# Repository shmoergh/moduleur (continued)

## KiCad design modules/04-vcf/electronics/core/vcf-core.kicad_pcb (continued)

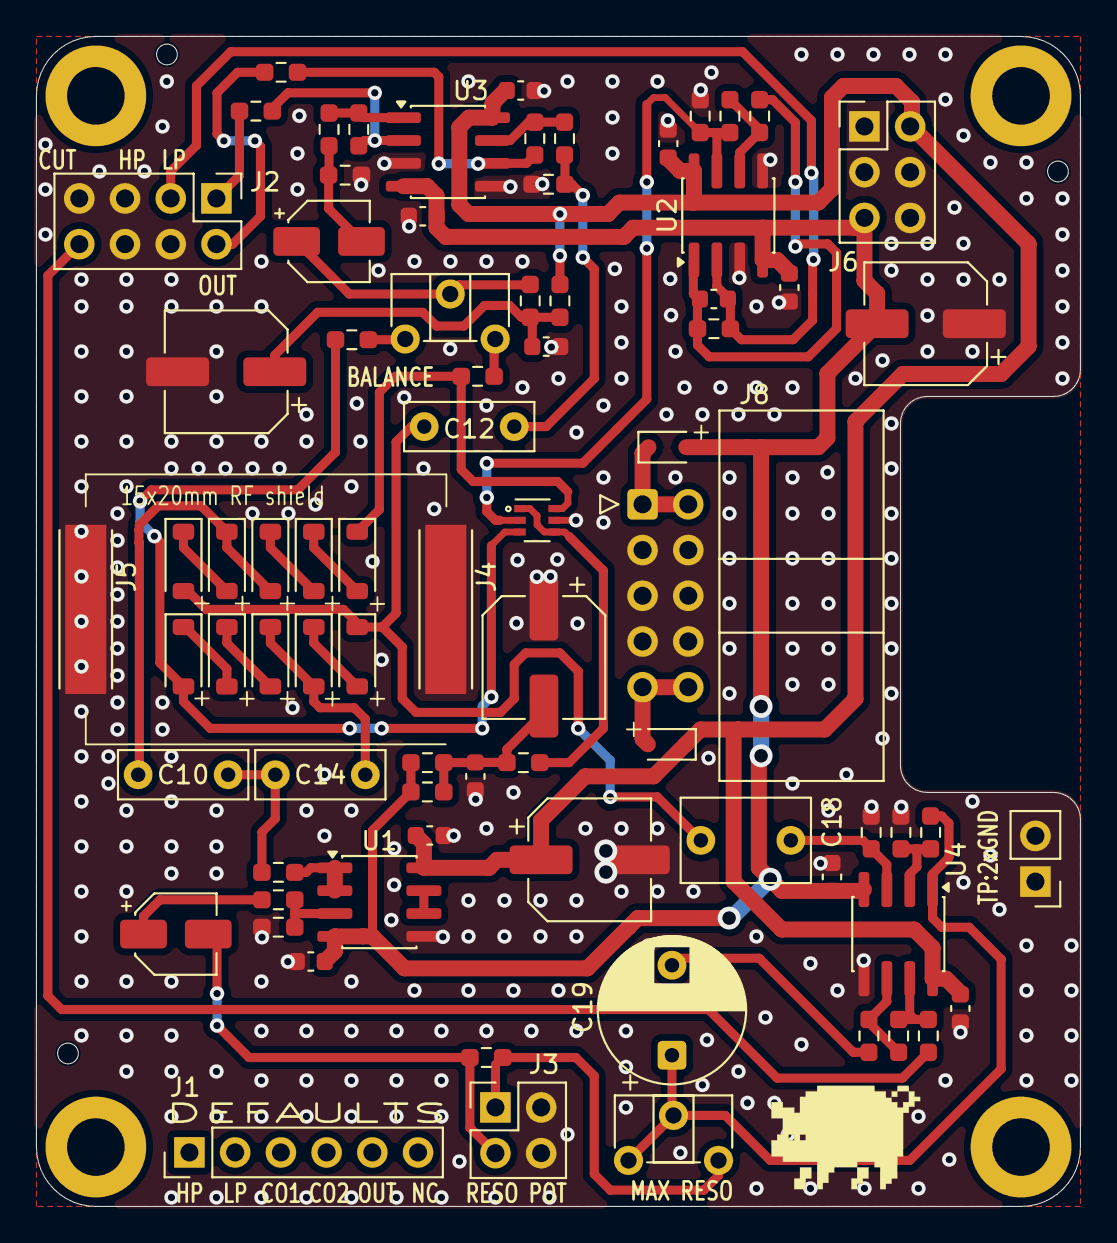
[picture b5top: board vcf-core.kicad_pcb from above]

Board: 2 copper layers, 58.0 x 65.0 mm, 82 parts (0 on the bottom side), 48 nets.

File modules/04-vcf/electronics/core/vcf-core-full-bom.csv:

"Reference","Qty","Value","Exclude from BOM","Footprint","LCSC","Part no.","Part URL","Vendor","CHECKED"
"C1,C2,C3,C4,C5,C6,C8,C9,C15,C16","10","100n","","Capacitor_SMD:C_0603_1608Metric","C14663","","","JLCPCB","YES"
"C7","1","10n","","Capacitor_SMD:C_0603_1608Metric","C57112","","","JLCPCB","YES"
"C10,C12,C14","3","1n (Foil)","","Capacitor_THT:C_Rect_L7.0mm_W2.5mm_P5.00mm","","80-R82EC1100SH50J ","https://mou.sr/3ZRLX4F","Mouser","YES"
"C11","1","2.2u","","Capacitor_SMD:CP_Elec_4x5.7","C249889","","","JLCPCB","YES"
"C13,C17,C21,C22","4","100u","","Capacitor_SMD:CP_Elec_6.3x7.7","C2836442","","","JLCPCB","YES"
"C18","1","1u (foil)","","Capacitor_THT:C_Rect_L7.0mm_W4.5mm_P5.00mm","","80-R82CC4100AA60J ","https://mou.sr/48MjAbl","Mouser","YES"
"C19","1","4.7u","","Capacitor_THT:CP_Radial_D8.0mm_P5.00mm","","80-ESK475M035AC3AA ","https://mou.sr/455uZSu","Mouser","YES"
"C20","1","10u","","Capacitor_SMD:CP_Elec_4x5.4","C3343","","","JLCPCB","YES"
"D1,D2,D3,D4,D5,D6,D7,D8,D9,D10","10","1N4148","","Diode_SMD:D_SOD-123","C81598","","","JLCPCB","YES"
"D11,D12","2","1N5817","","Diode_SMD:D_SOD-323","C5190152","","","JLCPCB","YES"
"H1,H2,H3,H4","4","MountingHole","Excluded from BOM","MountingHole:MountingHole_3.2mm_M3_DIN965_Pad","","","","X",""
"J1","1","Conn_01x06","","Connector_PinHeader_2.54mm:PinHeader_1x06_P2.54mm_Vertical","","200-SSW10401TMS","https://mou.sr/4puxA0F","Mouser","YES"
"J2","1","Conn_02x04_Counter_Clockwise","","Connector_PinHeader_2.54mm:PinHeader_2x04_P2.54mm_Vertical","","200-HTSW10407TD ","https://mou.sr/4nYsZDt","Mouser","YES"
"J3","1","Conn_02x02_Counter_Clockwise","","Connector_PinHeader_2.54mm:PinHeader_2x02_P2.54mm_Vertical","","200-HTSW10207TD","https://mou.sr/3TDBcz9","Mouser","YES"
"J4,J5","2","S1711-46R","Excluded from BOM","Shmoergh_Custom_Footprints:HARWIN_S1711-46R","","855-S1711-46R ","https://mou.sr/44w0zrg","Mouser","YES"
"J6","1","Conn_02x03_Odd_Even","","Connector_PinHeader_2.54mm:PinHeader_2x03_P2.54mm_Vertical","","200-TSW10307TD","https://mou.sr/4liCQlU","Mouser","YES"
"J7","1","Conn_01x02","","Connector_PinHeader_2.54mm:PinHeader_1x02_P2.54mm_Vertical","","200-HTSW10207TS","https://mou.sr/3IruU3e","Mouser","YES"
"J8","1","Conn_02x05_Odd_Even","","Connector_IDC:IDC-Header_2x05_P2.54mm_Horizontal","","571-5103310-1","https://mou.sr/3GwYxj9","Mouser","YES"
"Q1","1","BC847BS","","Package_TO_SOT_SMD:SOT-363_SC-70-6","C5380687","","","JLCPCB","YES"
"R1","1","20k","","Resistor_SMD:R_0603_1608Metric_Pad0.98x0.95mm_HandSolder","C4184","","","JLCPCB","YES"
"R4,R6,R8,R29","4","10k","","Resistor_SMD:R_0603_1608Metric_Pad0.98x0.95mm_HandSolder","C25804","","","JLCPCB","YES"
"R7","1","56k","","Resistor_SMD:R_0603_1608Metric_Pad0.98x0.95mm_HandSolder","C23206","","","JLCPCB","YES"
"R9,R26","2","47k","","Resistor_SMD:R_0603_1608Metric_Pad0.98x0.95mm_HandSolder","C25819","","","JLCPCB","YES"
"R10","1","200k","","Resistor_SMD:R_0603_1608Metric_Pad0.98x0.95mm_HandSolder","C25811","","","JLCPCB","YES"
"R11","1","180k","","Resistor_SMD:R_0603_1608Metric_Pad0.98x0.95mm_HandSolder","C3016400","","","JLCPCB","YES"
"R12","1","2.7k","","Resistor_SMD:R_0603_1608Metric_Pad0.98x0.95mm_HandSolder","C13167","","","JLCPCB","YES"
"R13,R22","2","1.5k","","Resistor_SMD:R_0603_1608Metric_Pad0.98x0.95mm_HandSolder","C22843","","","JLCPCB","YES"
"R14","1","2.2k","","Resistor_SMD:R_0603_1608Metric_Pad0.98x0.95mm_HandSolder","C4190","","","JLCPCB","YES"
"R15","1","33k","","Resistor_SMD:R_0603_1608Metric_Pad0.98x0.95mm_HandSolder","C4216","","","JLCPCB","YES"
"R16","1","100","","Resistor_SMD:R_0603_1608Metric_Pad0.98x0.95mm_HandSolder","C22775","","","JLCPCB","YES"
"R17","1","390","","Resistor_SMD:R_0603_1608Metric_Pad0.98x0.95mm_HandSolder","C23151","","","JLCPCB","YES"
"R18,R19,R23,R32","4","1k","","Resistor_SMD:R_0603_1608Metric_Pad0.98x0.95mm_HandSolder","C21190","","","JLCPCB","YES"
"R20","1","3.9k","","Resistor_SMD:R_0603_1608Metric_Pad0.98x0.95mm_HandSolder","C23018","","","JLCPCB","YES"
"R21","1","200","","Resistor_SMD:R_0603_1608Metric_Pad0.98x0.95mm_HandSolder","C8218","","","JLCPCB","YES"
"R24,R27","2","1M","","Resistor_SMD:R_0603_1608Metric_Pad0.98x0.95mm_HandSolder","C22935","","","JLCPCB","YES"
"R25","1","22k","","Resistor_SMD:R_0603_1608Metric_Pad0.98x0.95mm_HandSolder","C31850","","","JLCPCB","YES"
"R28","1","220k","","Resistor_SMD:R_0603_1608Metric_Pad0.98x0.95mm_HandSolder","C22961","","","JLCPCB","YES"
"R30,R31","2","100k","","Resistor_SMD:R_0603_1608Metric_Pad0.98x0.95mm_HandSolder","C25803","","","JLCPCB","YES"
"RV_BALANCE1","1","1k","","Potentiometer_THT:Potentiometer_ACP_CA6-H2,5_Horizontal","","531-PT6KH-1K ","https://mou.sr/3DgNY1x","Mouser","YES"
"RV_MAX_RESO1","1","100k","","Potentiometer_THT:Potentiometer_ACP_CA6-H2,5_Horizontal","","774-06TR4AA104CP","https://mou.sr/4oMQfnb","Mouser","YES"
"U1,U2,U3,U4","4","TL072","","Package_SO:SOIC-8_3.9x4.9mm_P1.27mm","C6961","","","JLCPCB","YES"

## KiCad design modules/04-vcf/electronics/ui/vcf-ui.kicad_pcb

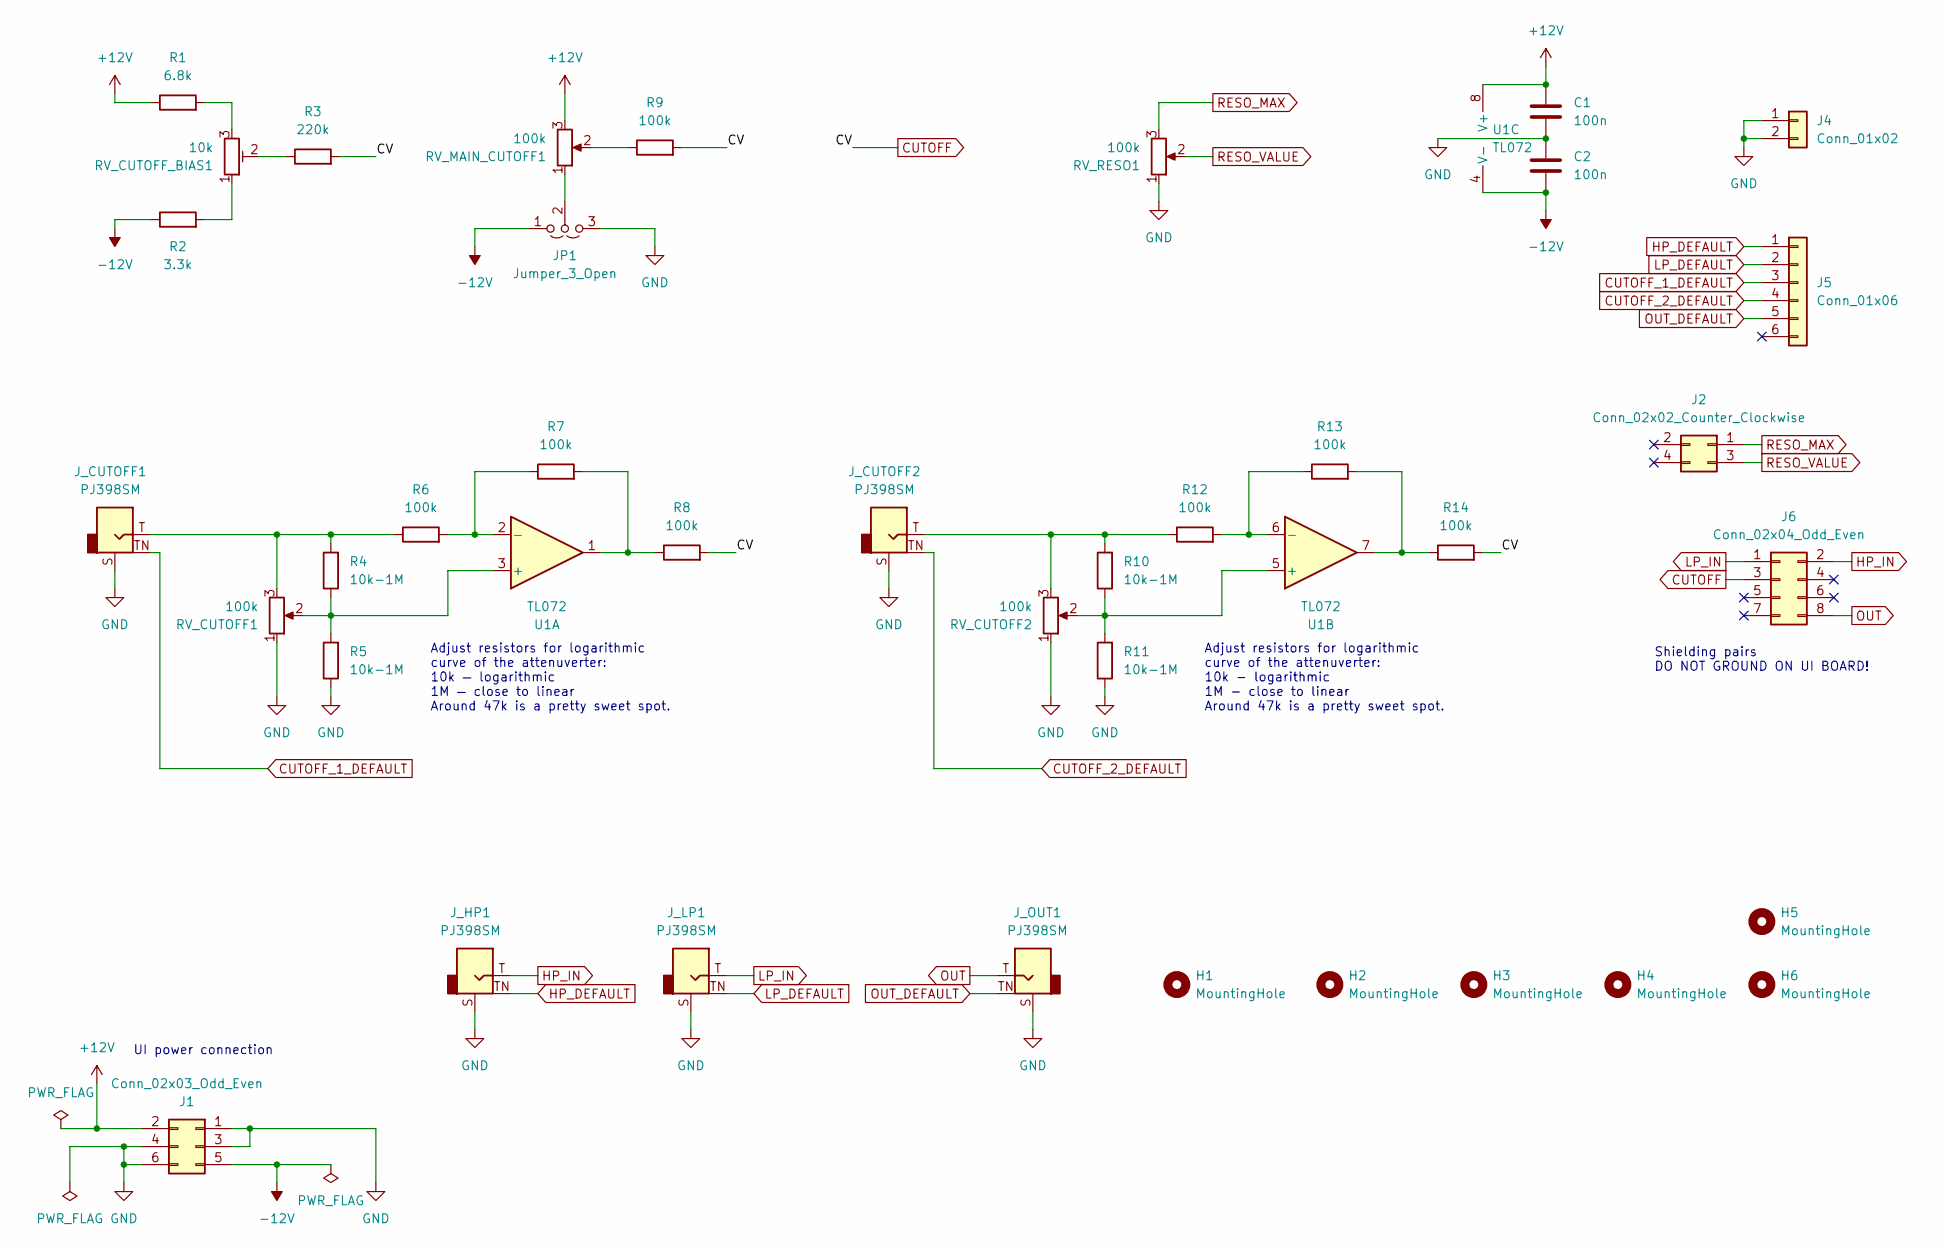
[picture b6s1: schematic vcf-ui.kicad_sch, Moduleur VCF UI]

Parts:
C1, C2: 100n; C_Disc_D5.0mm_W2.5mm_P2.50mm; Part no. 594-K104K15X7RF53L2
H1, H2, H3, H4, H5, H6: MountingHole; MountingHole_3.2mm_M3_DIN965_Pad
J1: Conn_02x03_Odd_Even; PinSocket_2x03_P2.54mm_Vertical; Part no. 200-SSW10301TD
J2: Conn_02x02_Counter_Clockwise; PinSocket_2x02_P2.54mm_Vertical; Part no. 200-SSW10206TD
J4: Conn_01x02; PinSocket_1x02_P2.54mm_Vertical; Part no. 200-SSW10201TS
J5: Conn_01x06; PinSocket_1x06_P2.54mm_Vertical; Part no. 200-SSW10601TS
J6: Conn_02x04_Odd_Even; PinSocket_2x04_P2.54mm_Vertical; Part no. 200-SSW10401TD
JP1: Jumper_3_Open; PinHeader_1x03_P2.54mm_Vertical
J_CUTOFF1, J_CUTOFF2: PJ398SM; Jack_3.5mm_QingPu_WQP-PJ398SM_Vertical_CircularHoles; Part no. PJ398SM
J_HP1: PJ398SM; Jack_3.5mm_QingPu_WQP-PJ398SM_Vertical_CircularHoles; Part no. PJ398SM
J_LP1: PJ398SM; Jack_3.5mm_QingPu_WQP-PJ398SM_Vertical_CircularHoles; Part no. PJ398SM
J_OUT1: PJ398SM; Jack_3.5mm_QingPu_WQP-PJ398SM_Vertical_CircularHoles; Part no. PJ398SM
R1: 6.8k; R_Axial_DIN0207_L6.3mm_D2.5mm_P7.62mm_Horizontal; Part no. 603-MFR-25FRF52100K
R2: 3.3k; R_Axial_DIN0207_L6.3mm_D2.5mm_P7.62mm_Horizontal; Part no. 603-MFR-25FRF52100K
R3: 220k; R_Axial_DIN0207_L6.3mm_D2.5mm_P7.62mm_Horizontal; Part no. 603-MFR-25FRF52100K
R4, R5, R10, R11: 10k-1M; R_Axial_DIN0207_L6.3mm_D2.5mm_P7.62mm_Horizontal; Part no. 603-MFR-25FRF52100K
R6, R7, R8, R9, R12, R13, R14: 100k; R_Axial_DIN0207_L6.3mm_D2.5mm_P7.62mm_Horizontal; Part no. 603-MFR-25FRF52100K
RV_CUTOFF1, RV_CUTOFF2: 100k; Potentiometer_Bourns_Single-PTV09A; Part no. 652-PTV09A4025UB104
RV_CUTOFF_BIAS1: 10k; Potentiometer_ACP_CA6-H2,5_Horizontal; Part no. 774-06TR4AA103CP
RV_MAIN_CUTOFF1: 100k; Potentiometer_Bourns_Single-PTV09A; Part no. 652-PTV09A4025UB104
RV_RESO1: 100k; Potentiometer_Bourns_Single-PTV09A; Part no. 652-PTV09A4025UB104
U1: TL072; DIP-8_W7.62mm_LongPads; Part no. 595-TL072CP

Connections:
+12V: C1.1, J1.2, R1.1, RV_MAIN_CUTOFF1.3, U1.8 (V+)
-12V: C2.2, J1.5, JP1.1 (A), R2.1, U1.4 (V-)
CUTOFF: J6.3, R3.2, R8.2, R9.2, R14.2
CUTOFF_1_DEFAULT: J5.3, J_CUTOFF1.TN
CUTOFF_2_DEFAULT: J5.4, J_CUTOFF2.TN
GND: C1.2, C2.1, J1.1, J1.3, J1.4, J1.6, J4.1, J4.2, JP1.3 (B), J_CUTOFF1.S, J_CUTOFF2.S, J_HP1.S, J_LP1.S, J_OUT1.S, R5.1, R11.1, RV_CUTOFF1.1, RV_CUTOFF2.1, RV_RESO1.1
HP_DEFAULT: J5.1, J_HP1.TN
HP_IN: J6.2, J_HP1.T
LP_DEFAULT: J5.2, J_LP1.TN
LP_IN: J6.1, J_LP1.T
unnamed: JP1.2 (C), RV_MAIN_CUTOFF1.1
unnamed: J_CUTOFF1.T, R4.2, R6.1, RV_CUTOFF1.3
unnamed: J_CUTOFF2.T, R10.2, R12.1, RV_CUTOFF2.3
unnamed: R1.2, RV_CUTOFF_BIAS1.3
unnamed: R2.2, RV_CUTOFF_BIAS1.1
unnamed: R3.1, RV_CUTOFF_BIAS1.2
unnamed: R7.2, R8.1, U1.1
unnamed: R9.1, RV_MAIN_CUTOFF1.2
unnamed: R13.2, R14.1, U1.7
unnamed: R4.1, R5.2, RV_CUTOFF1.2, U1.3 (+)
unnamed: R6.2, R7.1, U1.2 (-)
unnamed: R10.1, R11.2, RV_CUTOFF2.2, U1.5 (+)
unnamed: R12.2, R13.1, U1.6 (-)
OUT: J6.8, J_OUT1.T
OUT_DEFAULT: J5.5, J_OUT1.TN
RESO_MAX: J2.1, RV_RESO1.3
RESO_VALUE: J2.3, RV_RESO1.2

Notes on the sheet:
UI power connection
Adjust resistors for logarithmic curve of the attenuverter: 10k — logarithmic 1M — close to linear Around 47k is a pretty sweet spot.
Shielding pairs DO NOT GROUND ON UI BOARD!
Adjust resistors for logarithmic curve of the attenuverter: 10k - logarithmic 1M - close to linear Around 47k is a pretty sweet spot.

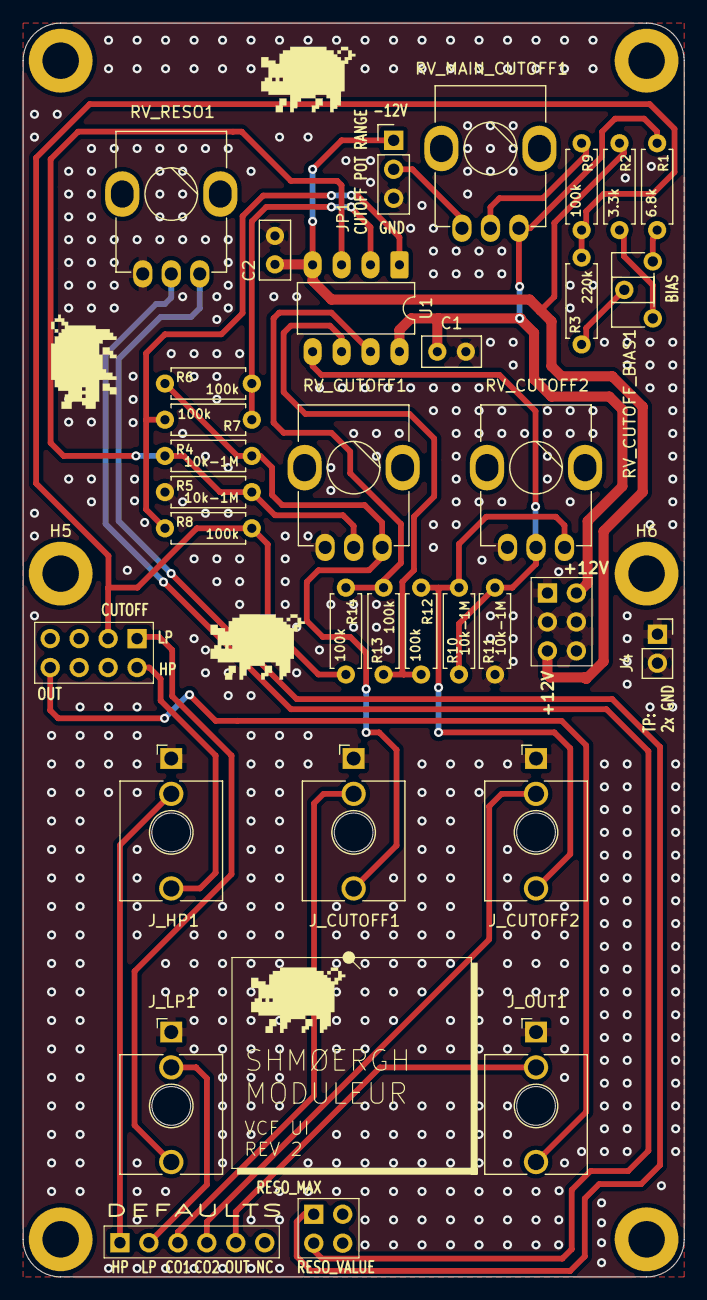
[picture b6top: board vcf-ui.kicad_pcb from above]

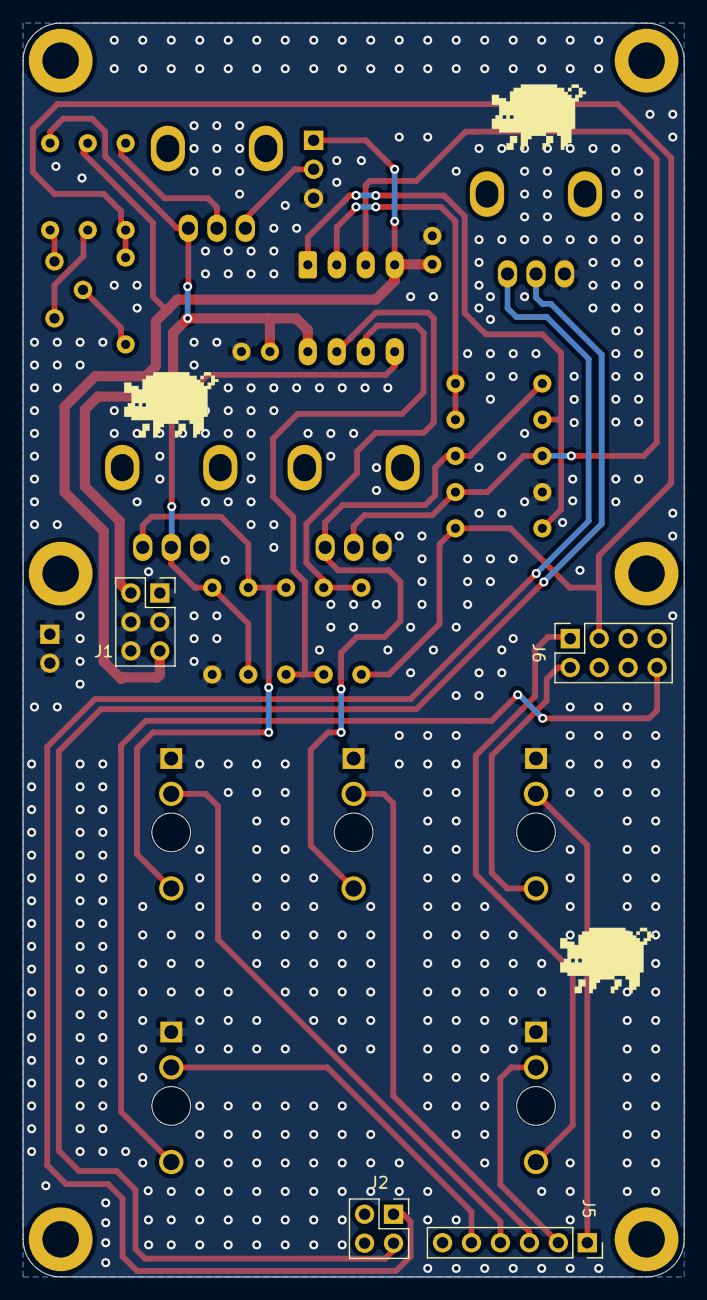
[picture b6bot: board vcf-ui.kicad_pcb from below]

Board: 2 copper layers, 58.0 x 110.0 mm, 39 parts (4 on the bottom side), 27 nets.

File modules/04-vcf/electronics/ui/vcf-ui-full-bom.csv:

"Reference","Qty","Value","DNP","Exclude from BOM","Exclude from Board","Footprint","Datasheet","Part no.","Part URL","Vendor","Note"
"C1,C2","2","100n","","","","Capacitor_THT:C_Disc_D5.0mm_W2.5mm_P2.50mm","~","594-K104K15X7RF53L2","https://mou.sr/4adMnbf","Mouser",""
"J1","1","Conn_02x03_Odd_Even","","","","Connector_PinSocket_2.54mm:PinSocket_2x03_P2.54mm_Vertical","~","200-SSW10301TD","https://mou.sr/3GIDVEr","Mouser",""
"J2","1","Conn_02x02_Counter_Clockwise","","","","Connector_PinSocket_2.54mm:PinSocket_2x02_P2.54mm_Vertical","~","200-SSW10206TD","https://mou.sr/4eSbYqI","Mouser",""
"J4","1","Conn_01x02","","","","Connector_PinSocket_2.54mm:PinSocket_1x02_P2.54mm_Vertical","~","200-SSW10201TS","https://mou.sr/4lBvdHe","Mouser",""
"J5","1","Conn_01x06","","","","Connector_PinSocket_2.54mm:PinSocket_1x06_P2.54mm_Vertical","~","200-SSW10601TS","https://mou.sr/4lnf48h","Mouser",""
"J6","1","Conn_02x04_Odd_Even","","","","Connector_PinSocket_2.54mm:PinSocket_2x04_P2.54mm_Vertical","~","200-SSW10401TD","https://mou.sr/4qqxl75","Mouser",""
"J_CUTOFF1,J_CUTOFF2,J_HP1,J_LP1,J_OUT1","5","PJ398SM","","","","Shmoergh_Custom_Footprints:Jack_3.5mm_QingPu_WQP-PJ398SM_Vertical_CircularHoles","~","PJ398SM","https://www.thonk.co.uk/shop/thonkiconn/","Thonk",""
"R1","1","6.8k","","","","Shmoergh_Custom_Footprints:R_Axial_DIN0207_L6.3mm_D2.5mm_P7.62mm_Horizontal","~","603-MFR-25FRF52100K","https://mou.sr/4hEwI4G","Mouser",""
"R2","1","3.3k","","","","Shmoergh_Custom_Footprints:R_Axial_DIN0207_L6.3mm_D2.5mm_P7.62mm_Horizontal","~","603-MFR-25FRF52100K","https://mou.sr/4hEwI4G","Mouser",""
"R3","1","220k","","","","Shmoergh_Custom_Footprints:R_Axial_DIN0207_L6.3mm_D2.5mm_P7.62mm_Horizontal","~","603-MFR-25FRF52100K","https://mou.sr/4hEwI4G","Mouser",""
"R4,R5,R10,R11","4","10k-1M","","","","Shmoergh_Custom_Footprints:R_Axial_DIN0207_L6.3mm_D2.5mm_P7.62mm_Horizontal","~","603-MFR-25FRF52100K","https://mou.sr/4hEwI4G","Mouser",""
"R6,R7,R8,R9,R12,R13,R14","7","100k","","","","Shmoergh_Custom_Footprints:R_Axial_DIN0207_L6.3mm_D2.5mm_P7.62mm_Horizontal","~","603-MFR-25FRF52100K","https://mou.sr/4hEwI4G","Mouser",""
"RV_CUTOFF1,RV_CUTOFF2,RV_MAIN_CUTOFF1,RV_RESO1","4","100k","","","","Shmoergh_Custom_Footprints:Potentiometer_Bourns_Single-PTV09A","~","652-PTV09A4025UB104","https://mou.sr/41lYe2k","Mouser","Knurled Shaft"
"RV_CUTOFF_BIAS1","1","10k","","","","Potentiometer_THT:Potentiometer_ACP_CA6-H2,5_Horizontal","~","774-06TR4AA103CP","https://mou.sr/44pTlq5","Mouser",""
"U1","1","TL072","","","","Package_DIP:DIP-8_W7.62mm_LongPads","http://www.ti.com/lit/ds/symlink/tl071.pdf","595-TL072CP","https://mou.sr/48zN39J","Mouser",""
